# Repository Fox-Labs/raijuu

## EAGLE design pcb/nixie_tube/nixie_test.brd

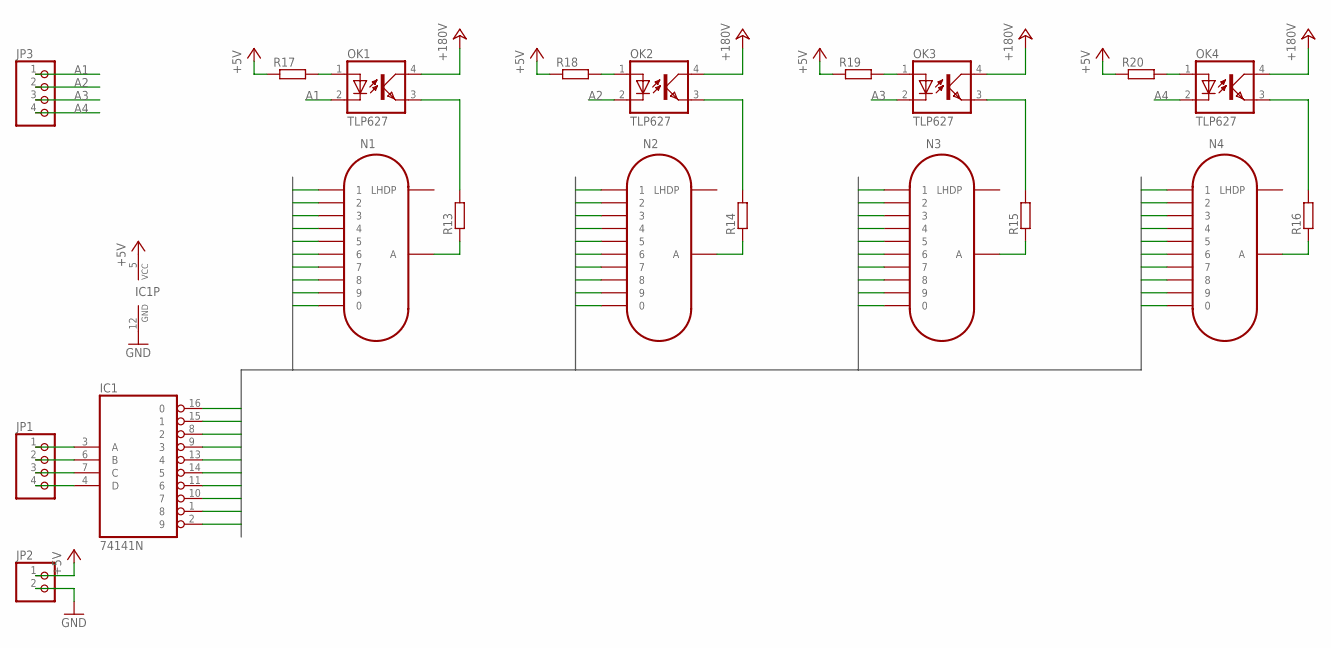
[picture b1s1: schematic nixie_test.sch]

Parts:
IC1: 74141N; DIL16
JP1, JP3: PINHD-1X4; 1X04
JP2: PINHD-1X2; 1X02
N1, N2, N3, N4: IN-12B; IN-12
OK1, OK2, OK3, OK4: TLP627; 4-SMD
R13, R14, R15, R16, R17, R18, R19, R20: R-EU_10; 0207/10

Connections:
+5V: IC1.5 (VCC), JP2.1, R17.1, R18.1, R19.1, R20.1
+24V: OK1.4 (COL), OK2.4 (COL), OK3.4 (COL), OK4.4 (COL); also elsewhere on the board
A1: JP3.1, OK1.2 (C)
A2: JP3.2, OK2.2 (C)
A3: JP3.3, OK3.2 (C)
A4: JP3.4, OK4.2 (C)
C0: IC1.16 (0), N1.0, N2.0, N3.0, N4.0
C1: IC1.15 (1), N1.1, N2.1, N3.1, N4.1
C2: IC1.8 (2), N1.2, N2.2, N3.2, N4.2
C3: IC1.9 (3), N1.3, N2.3, N3.3, N4.3
C4: IC1.13 (4), N1.4, N2.4, N3.4, N4.4
C5: IC1.14 (5), N1.5, N2.5, N3.5, N4.5
C6: IC1.11 (6), N1.6, N2.6, N3.6, N4.6
C7: IC1.10 (7), N1.7, N2.7, N3.7, N4.7
C8: IC1.1 (8), N1.8, N2.8, N3.8, N4.8
C9: IC1.2 (9), N1.9, N2.9, N3.9, N4.9
GND: IC1.12 (GND), JP2.2; also elsewhere on the board
unnamed: IC1.3 (A), JP1.1
unnamed: IC1.6 (B), JP1.2
unnamed: IC1.7 (C), JP1.3
unnamed: IC1.4 (D), JP1.4
unnamed: N1.A, R13.1
unnamed: OK1.3 (EMIT), R13.2
unnamed: N2.A, R14.1
unnamed: OK2.3 (EMIT), R14.2
unnamed: N3.A, R15.1
unnamed: OK3.3 (EMIT), R15.2
unnamed: N4.A, R16.1
unnamed: OK4.3 (EMIT), R16.2
unnamed: OK1.1 (A), R17.2
unnamed: OK2.1 (A), R18.2
unnamed: OK3.1 (A), R19.2
unnamed: OK4.1 (A), R20.2

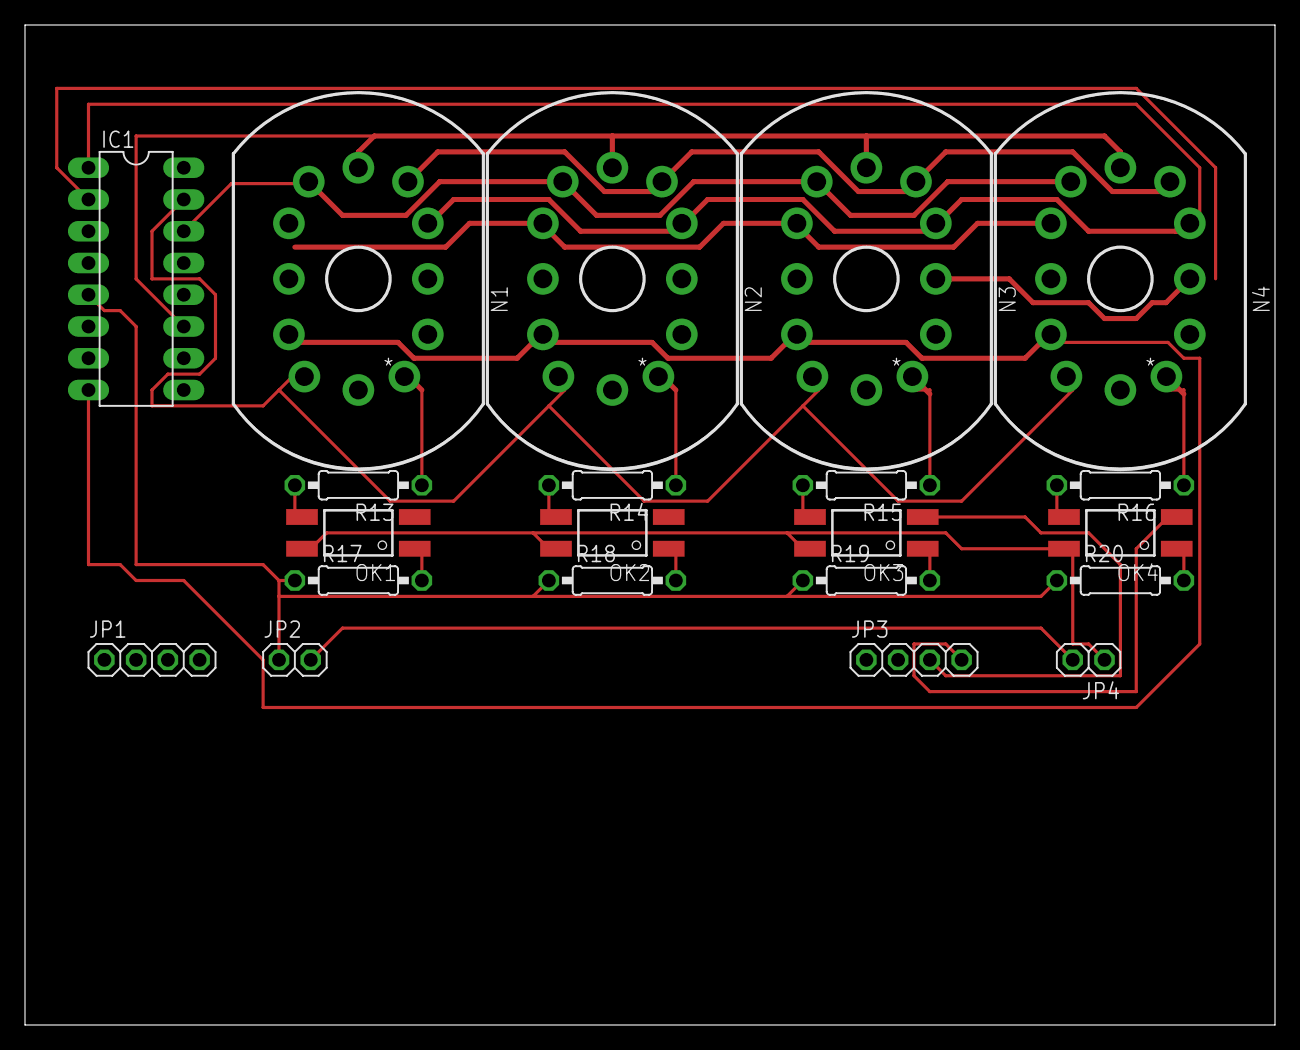
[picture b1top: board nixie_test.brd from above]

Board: 2 copper layers, 100.0 x 80.0 mm, 21 parts (0 on the bottom side), 33 nets.

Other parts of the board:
JP4: 1X02

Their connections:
+24V: JP4.1; also elsewhere on the board
GND: JP4.2; also elsewhere on the board

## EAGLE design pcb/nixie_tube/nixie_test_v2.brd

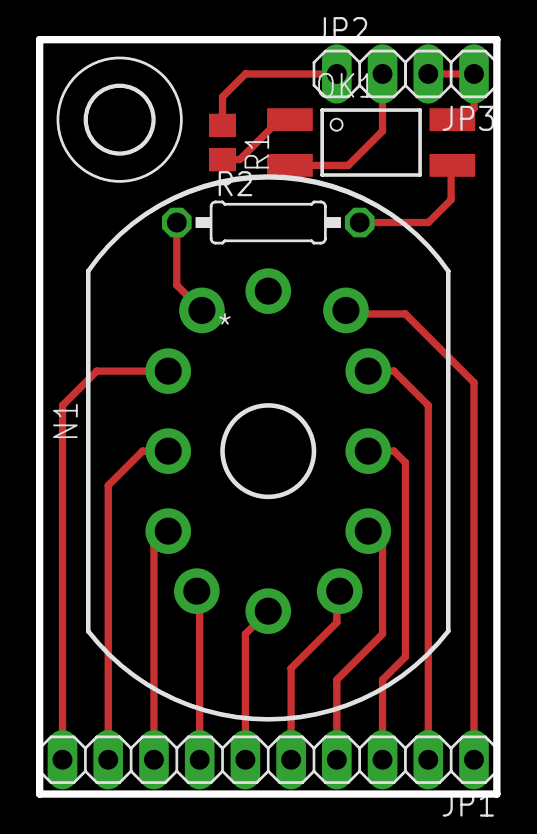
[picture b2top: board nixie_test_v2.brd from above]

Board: 2 copper layers, 25.4 x 41.9 mm, 8 parts (0 on the bottom side), 16 nets.

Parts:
JP1: 1X10
JP2, JP3: 1X02
N1: IN-12B; IN-12
OK1: TLP627; 4-SMD
R1: R0805
R2: 0207/10
U$1: 3,6

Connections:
+5V: JP2.1, R1.1
+24V: JP3.1, JP3.2, OK1.4
C0: JP1.10, N1.0
C1: JP1.1, N1.1
C2: JP1.2, N1.2
C3: JP1.3, N1.3
C4: JP1.4, N1.4
C5: JP1.5, N1.5
C6: JP1.6, N1.6
C7: JP1.7, N1.7
C8: JP1.8, N1.8
C9: JP1.9, N1.9
unnamed: JP2.2, OK1.2
unnamed: N1.A, R2.1
unnamed: OK1.3, R2.2
unnamed: OK1.1, R1.2

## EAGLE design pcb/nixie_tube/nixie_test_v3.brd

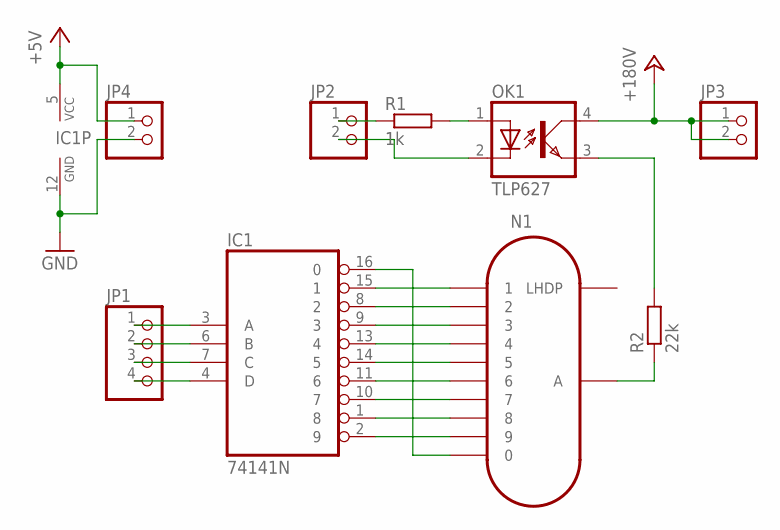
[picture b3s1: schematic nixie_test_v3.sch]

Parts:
IC1: 74141N; DIL16
JP1: PINHD-1X4; 1X04
JP2, JP3, JP4: PINHD-1X2; 1X02
N1: IN-12B; IN-12
OK1: TLP627; 4-SMD
R1: 1k; R0805
R2: 22k; 0207/10

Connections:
+5V: IC1.5 (VCC), JP4.1
+180V: JP3.1, JP3.2, OK1.4 (COL)
A: IC1.3 (A), JP1.1
B: IC1.6 (B), JP1.2
C: IC1.7 (C), JP1.3
C0: IC1.16 (0), N1.0
C1: IC1.15 (1), N1.1
C2: IC1.8 (2), N1.2
C3: IC1.9 (3), N1.3
C4: IC1.13 (4), N1.4
C5: IC1.14 (5), N1.5
C6: IC1.11 (6), N1.6
C7: IC1.10 (7), N1.7
C8: IC1.1 (8), N1.8
C9: IC1.2 (9), N1.9
D: IC1.4 (D), JP1.4
GND: IC1.12 (GND), JP4.2
LA: JP2.1, R1.1
LK: JP2.2, OK1.2 (C)
unnamed: N1.A, R2.1
unnamed: OK1.3 (EMIT), R2.2
unnamed: OK1.1 (A), R1.2

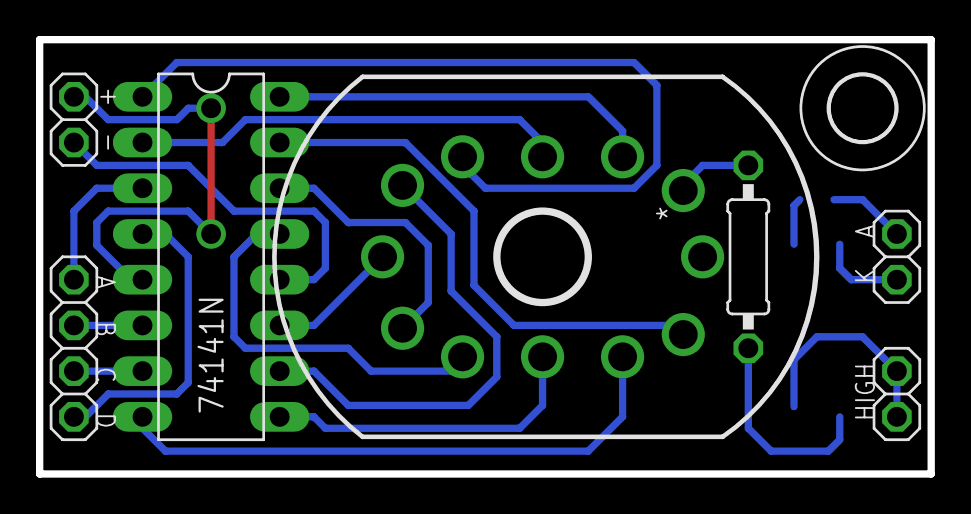
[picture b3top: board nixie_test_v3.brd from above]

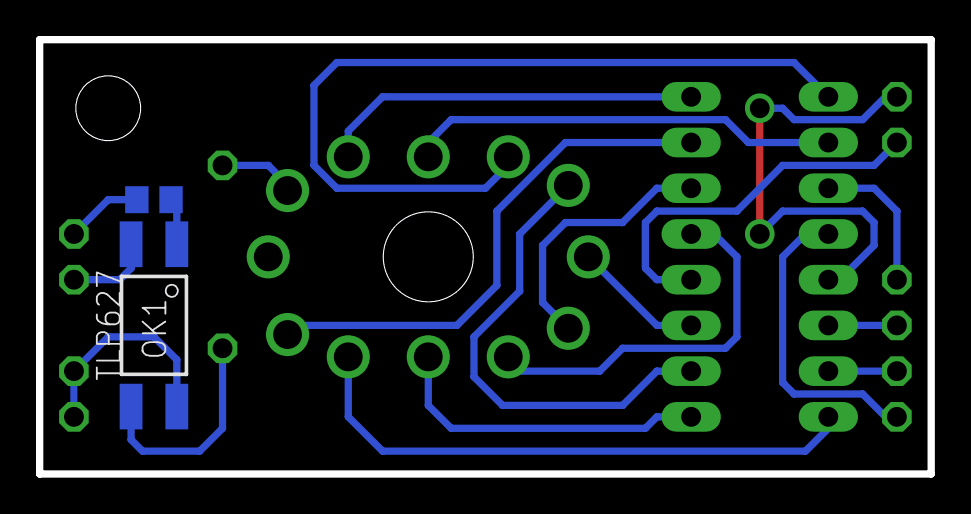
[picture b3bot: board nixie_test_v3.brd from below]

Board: 2 copper layers, 49.5 x 24.1 mm, 10 parts (2 on the bottom side), 22 nets.

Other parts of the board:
U$1: 3,6
